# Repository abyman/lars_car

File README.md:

# lars_car
This project is an intel edison installed into a RC car. 
The edison controls some motors and leds in the RC car.

aaron.byman@gmail.com

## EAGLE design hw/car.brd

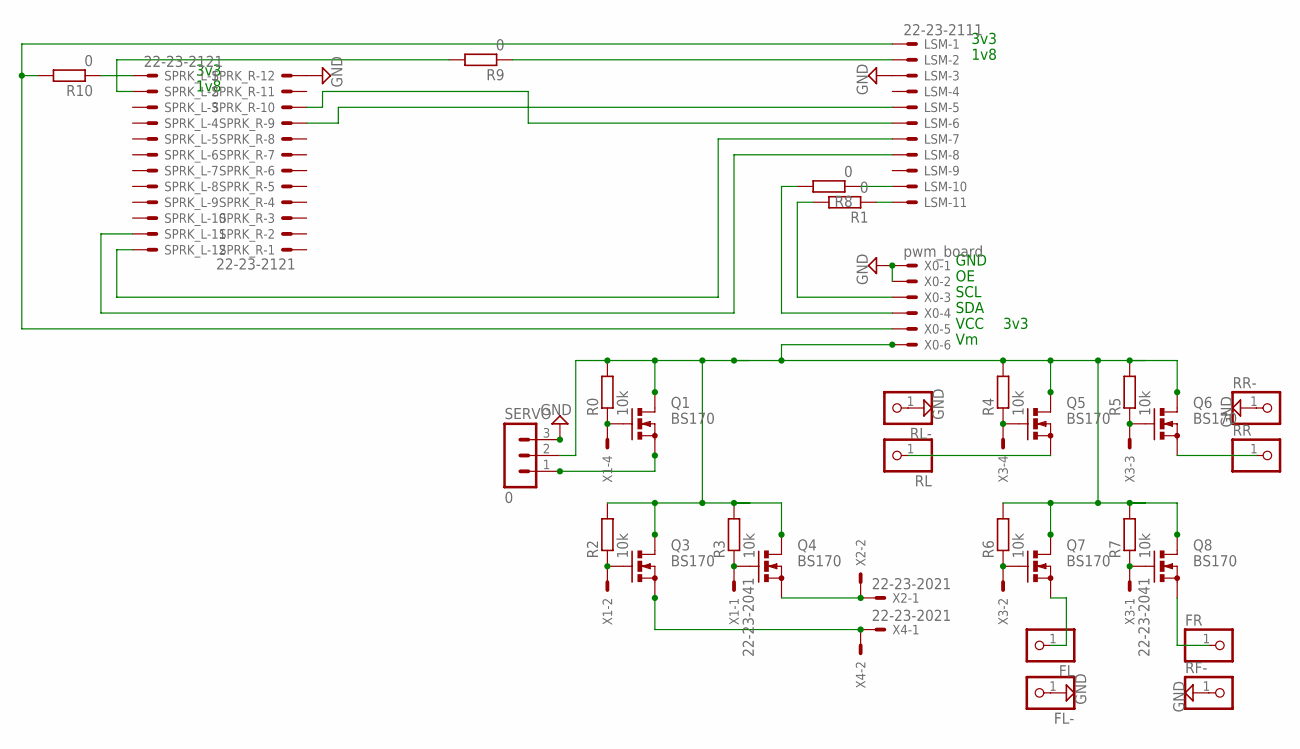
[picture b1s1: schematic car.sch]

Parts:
FL: PINHD-1X1; 1X01
FL-: PINHD-1X1; 1X01
FR: PINHD-1X1; 1X01
LSM: 22-23-2111
Q1, Q3, Q4, Q5, Q6, Q7, Q8: BS170; SOT54E
R0, R2, R3, R4, R5, R6, R7: 10k; 0207/10
R1, R8, R9, R10: 0; 0207/10
RF-: PINHD-1X1; 1X01
RL: PINHD-1X1; 1X01
RL-: PINHD-1X1; 1X01
RR: PINHD-1X1; 1X01
RR-: PINHD-1X1; 1X01
SERVO: 0; MA03-1
SPRK_L: 22-23-2121
SPRK_R: 22-23-2121
X0: pwm_board; 22-23-2061
X1, X3: 22-23-2041
X2, X4: 22-23-2021

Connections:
1V8: LSM.2, R9.1
FILL: LSM.10, R8.1
GND: FL-.1, LSM.3, RF-.1, RL-.1, RR-.1, SERVO.3, SPRK_R.12, X0.1, X0.2
unnamed: Q1.G, R0.1, X1.4
unnamed: Q4.S, X2.1, X2.2
unnamed: Q3.G, R2.1, X1.2
unnamed: Q4.G, R3.1, X1.1
unnamed: Q1.S, SERVO.1
unnamed: Q5.S, RL.1
unnamed: Q6.S, RR.1
unnamed: Q3.S, X4.1, X4.2
unnamed: FR.1, Q8.S
unnamed: Q5.G, R4.1, X3.4
unnamed: Q6.G, R5.1, X3.3
unnamed: Q7.G, R6.1, X3.2
unnamed: Q8.G, R7.1, X3.1
unnamed: FL.1, Q7.S
unnamed: LSM.11, R1.1
unnamed: R9.2, SPRK_L.2
unnamed: R8.2, X0.4
unnamed: R1.2, X0.3
unnamed: LSM.8, SPRK_L.11
unnamed: LSM.7, SPRK_L.12
unnamed: R10.1, SPRK_L.1
unnamed: LSM.5, SPRK_R.9
unnamed: LSM.6, SPRK_R.10
V3V3: LSM.1, R10.2, X0.5
VM: Q1.D, Q3.D, Q4.D, Q5.D, Q6.D, Q7.D, Q8.D, R0.2, R2.2, R3.2, R4.2, R5.2, R6.2, R7.2, SERVO.2, X0.6

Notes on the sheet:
GND
SCL
SDA
VCC
3v3
1v8

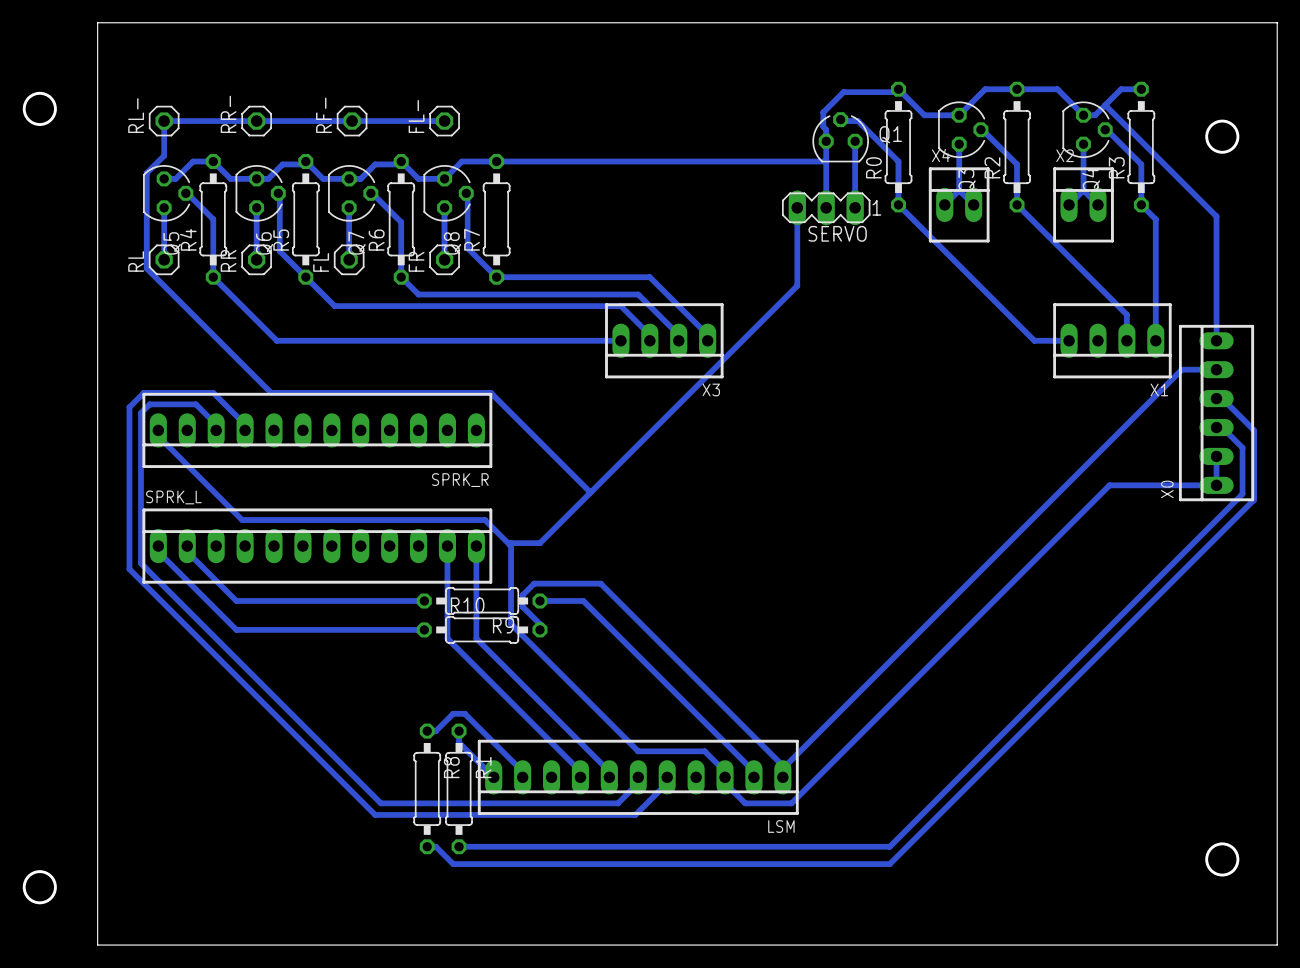
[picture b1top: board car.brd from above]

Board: 2 copper layers, 110.0 x 80.8 mm, 35 parts (0 on the bottom side), 28 nets.

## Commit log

2015-10-25 git repo created
2015-10-25 added readme
2015-11-15 added input t mode.
2015-11-25 Added light control
2015-11-25 Added schematics to repo
2015-11-25 updated schematics
2015-11-27 layout started
2015-11-30 layout v1 done
2015-12-17 layout again
2015-12-22 final layout
